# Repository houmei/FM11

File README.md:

## FM11

# FM11RAM
FM-11用のメインメモリ拡張カード  
[FM11RAM V01L02 完成](http://blog.livedoor.jp/hardyboy/archives/9856888.html)

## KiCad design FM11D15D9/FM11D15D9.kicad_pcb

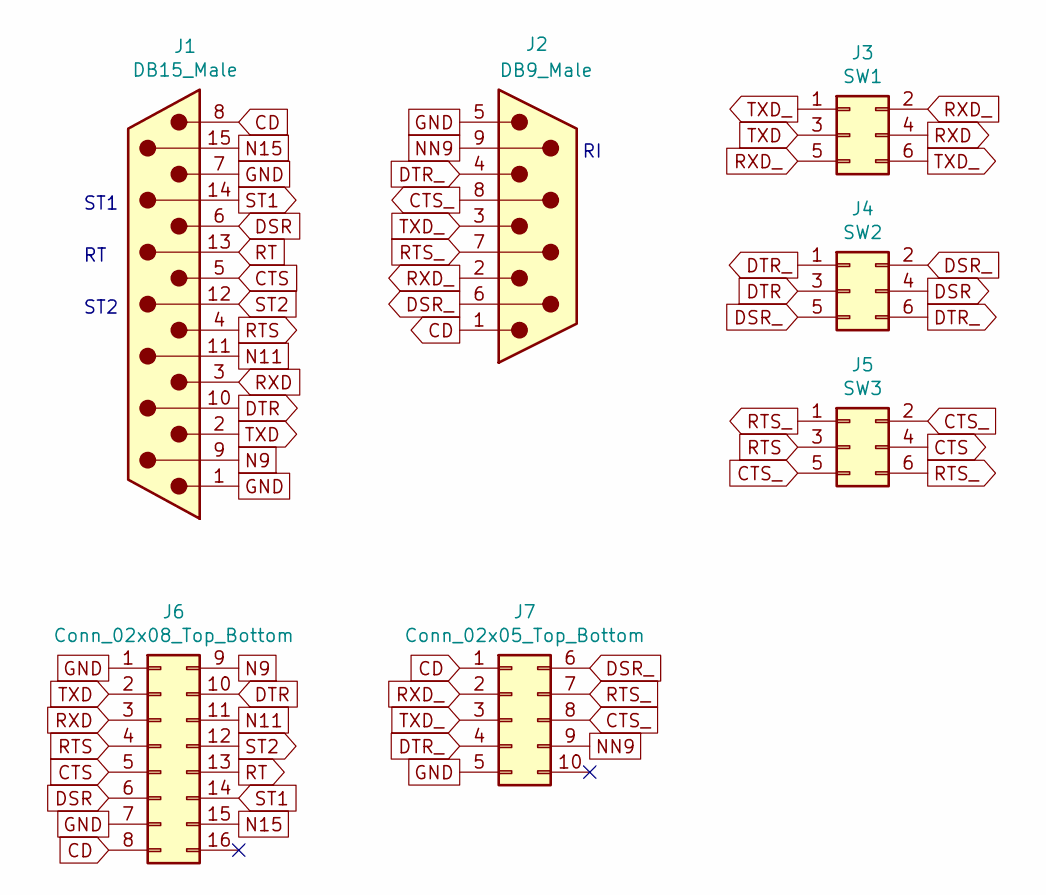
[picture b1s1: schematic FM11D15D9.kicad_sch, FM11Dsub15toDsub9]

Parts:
J1: DB15_Male; DSUB-15_Male_EdgeMount_P2.77mm
J2: DB9_Male; DSUB-9_Male_EdgeMount_P2.77mm
J3: SW1; PinHeader_2x03_P2.54mm_Vertical
J4: SW2; PinHeader_2x03_P2.54mm_Vertical
J5: SW3; PinHeader_2x03_P2.54mm_Vertical
J6: Conn_02x08_Top_Bottom; PinHeader_2x08_P2.54mm_Vertical
J7: Conn_02x05_Top_Bottom; PinHeader_2x05_P2.54mm_Vertical

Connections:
CD: J1.8, J2.1, J6.8, J7.1
CTS: J1.5, J5.4, J6.5
CTS_: J2.8, J5.2, J5.5, J7.8
DSR: J1.6, J4.4, J6.6
DSR_: J2.6, J4.2, J4.5, J7.6
DTR: J1.10, J4.3, J6.10
DTR_: J2.4, J4.1, J4.6, J7.4
GND: J1.1, J1.7, J2.5, J6.1, J6.7, J7.5
N9: J1.9, J6.9
N11: J1.11 (P111), J6.11
N15: J1.15, J6.15
NN9: J2.9, J7.9
RT: J1.13, J6.13
RTS: J1.4, J5.3, J6.4
RTS_: J2.7, J5.1, J5.6, J7.7
RXD: J1.3, J3.4, J6.3
RXD_: J2.2, J3.2, J3.5, J7.2
ST1: J1.14, J6.14
ST2: J1.12, J6.12
TXD: J1.2, J3.3, J6.2
TXD_: J2.3, J3.1, J3.6, J7.3

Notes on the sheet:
ST2
ST1

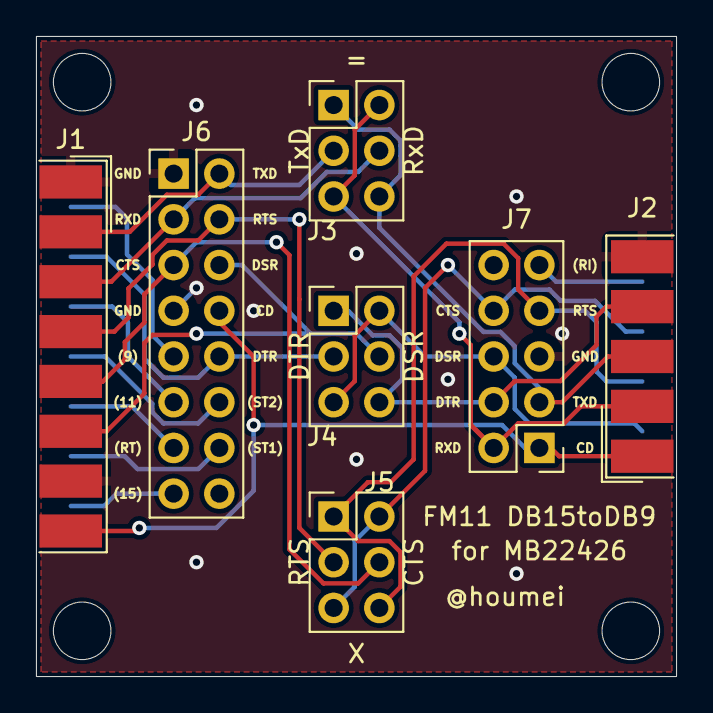
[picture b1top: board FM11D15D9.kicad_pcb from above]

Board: 2 copper layers, 35.6 x 35.6 mm, 7 parts (0 on the bottom side), 21 nets.

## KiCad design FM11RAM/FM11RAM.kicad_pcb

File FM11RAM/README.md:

# FM11RAM - RAM for FM-11

Schematic  

PCB  

## 説明

[FM11RAM V01L02 完成](http://blog.livedoor.jp/hardyboy/archives/9856888.html "まごころせいじつ堂")  
[FM11RAM説明書](https://keisanki.booth.pm/items/3207905)

販売中  
[FM11RAM (キット)](https://keisanki.booth.pm/items/3209883 "まごころせいじつ堂")  
[FM11 RAM(1MB)キット](https://www.beep-shop.com/ec/products/detail/DI-1--15633 "BEEP")

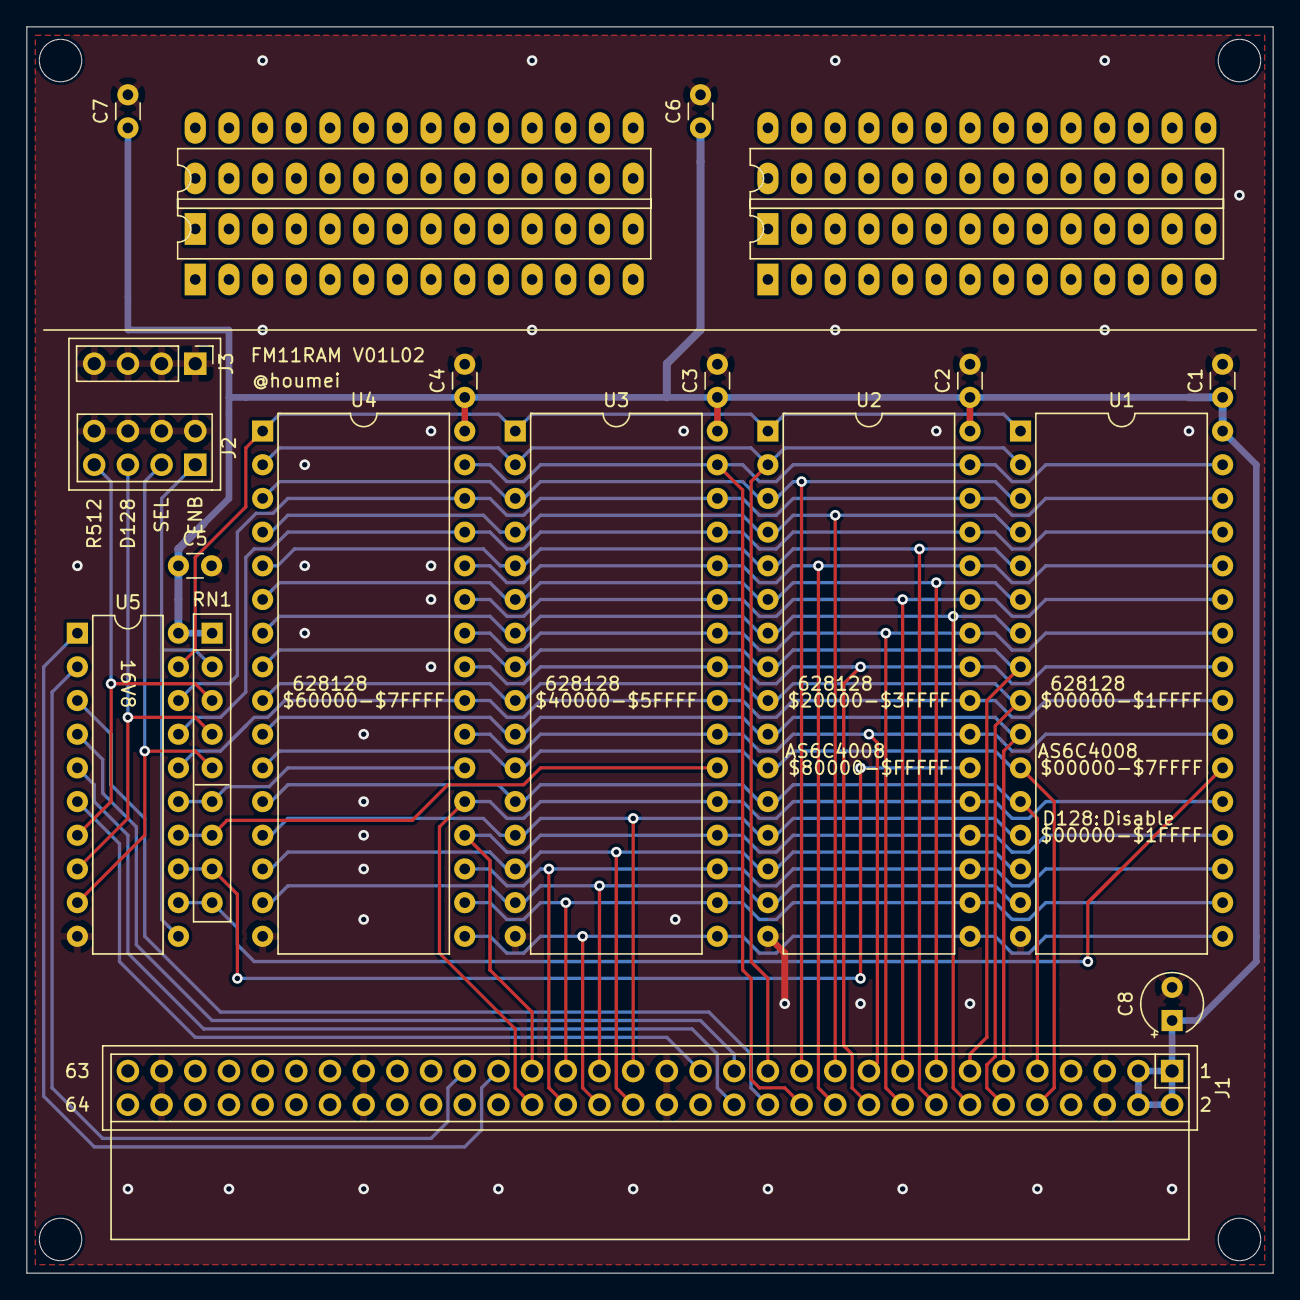
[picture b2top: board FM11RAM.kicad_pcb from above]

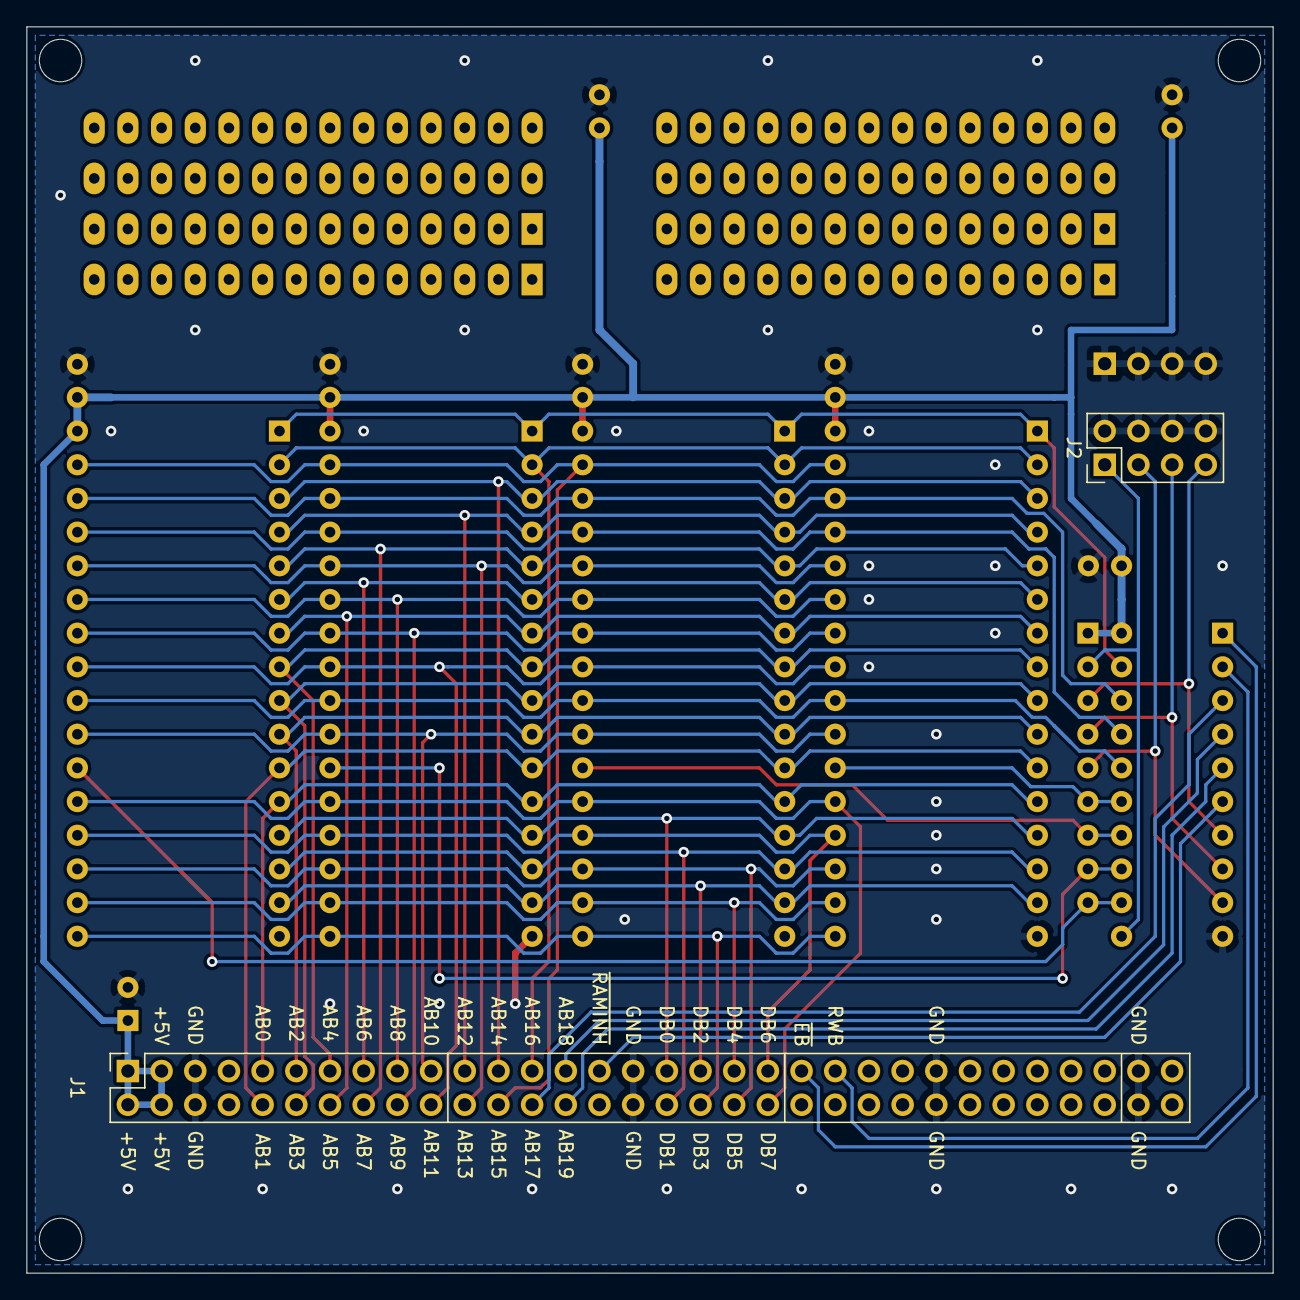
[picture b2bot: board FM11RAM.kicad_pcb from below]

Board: 2 copper layers, 94.0 x 94.0 mm, 21 parts (2 on the bottom side), 45 nets.

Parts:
C1, C2, C3, C4, C5, C6, C7: 0.1uF; C_Disc_D3.0mm_W1.6mm_P2.50mm
C8: 10uF; CP_Radial_Tantal_D4.5mm_P2.50mm
J1: Conn_02x32_Odd_Even; PinSocket_2x32_P2.54mm_Vertical
J2: DIP4W; PinHeader_2x04_P2.54mm_Vertical
J3: Conn_01x04_Male; PinHeader_1x04_P2.54mm_Vertical
RN1: 10K; R_Array_SIP9
U1, U2, U3, U4: AS6C4008-55PCN; DIP-32_W15.24mm
U5: GAL16V8; DIP-20_W7.62mm
U6, U6#2, U7, U7#2: HM62256BLP; DIP-28_W7.62mm_LongPads

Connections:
+5V: C1.1, C2.1, C3.1, C4.1, C5.1, C6.1, C7.1, C8.1, J1.1, J1.2, J1.3, J1.4, RN1.1, U1.32, U2.32, U3.32, U4.32, U5.20
/~512: J2.7, RN1.3, U5.7
/~D128: J2.5, RN1.4, U5.8
/~ENABLE: J2.1, RN1.2, U5.11
/~SEL: J2.3, RN1.5, U5.9
A17CS2: U1.30, U2.30, U3.30, U4.30, U5.18
A18NC: U1.1, U2.1, U3.1, U4.1, U5.19
AB0: J1.9, U1.12, U2.12, U3.12, U4.12
AB1: J1.10, U1.11, U2.11, U3.11, U4.11
AB2: J1.11, U1.10, U2.10, U3.10, U4.10
AB3: J1.12, U1.9, U2.9, U3.9, U4.9
AB4: J1.13, U1.8, U2.8, U3.8, U4.8
AB5: J1.14, U1.7, U2.7, U3.7, U4.7
AB6: J1.15, U1.6, U2.6, U3.6, U4.6
AB7: J1.16, U1.5, U2.5, U3.5, U4.5
AB8: J1.17, U1.27, U2.27, U3.27, U4.27
AB9: J1.18, U1.26, U2.26, U3.26, U4.26
AB10: J1.19, U1.23, U2.23, U3.23, U4.23
AB11: J1.20, U1.25, U2.25, U3.25, U4.25
AB12: J1.21, U1.4, U2.4, U3.4, U4.4
AB13: J1.22, U1.28, U2.28, U3.28, U4.28
AB14: J1.23, U1.3, U2.3, U3.3, U4.3
AB15: J1.24, U1.31, U2.31, U3.31, U4.31
AB16: J1.25, U1.2, U2.2, U3.2, U4.2
AB17: J1.26, U5.3
AB18: J1.27, U5.4
AB19: J1.28, U5.5
DB0: J1.33, U1.13, U2.13, U3.13, U4.13
DB1: J1.34, U1.14, U2.14, U3.14, U4.14
DB2: J1.35, U1.15, U2.15, U3.15, U4.15
DB3: J1.36, U1.17, U2.17, U3.17, U4.17
DB4: J1.37, U1.18, U2.18, U3.18, U4.18
DB5: J1.38, U1.19, U2.19, U3.19, U4.19
DB6: J1.39, U1.20, U2.20, U3.20, U4.20
DB7: J1.40, U1.21, U2.21, U3.21, U4.21
GND: C1.2, C2.2, C3.2, C4.2, C5.2, C6.2, C7.2, C8.2, J1.5, J1.6, J1.31, J1.32, J1.49, J1.50, J1.61, J1.62, J2.2, J2.4, J2.6, J2.8, J3.1, J3.2, J3.3, J3.4, U1.16, U2.16, U3.16, U4.16, U5.10
RWB: J1.43, U5.2
~CE0: RN1.9, U1.22, U5.12
~CE1: RN1.8, U2.22, U5.13
~CE2: RN1.7, U3.22, U5.14
~CE3: RN1.6, U4.22, U5.15
~EB: J1.41, U5.1
~OE: U1.24, U2.24, U3.24, U4.24, U5.16
~RAMIHB: J1.29, U5.6
~WE: U1.29, U2.29, U3.29, U4.29, U5.17
